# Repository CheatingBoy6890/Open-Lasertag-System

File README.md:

# Openlasertag-System
##This isn't maintained anymore and to be honest never really worked. Please have a look at Open-Lasertag-System-Tagger, we're continuing work there. 
--
Openlasertag-System is a project for the ESP32 and ESP8266 that aims
to make a Lasertag playebla for everyone without needing to setup a Wifi, servers etc.
---
The project is currently in Alpha state and not yet tested, but I'm trying my best to progress as fast as possible.

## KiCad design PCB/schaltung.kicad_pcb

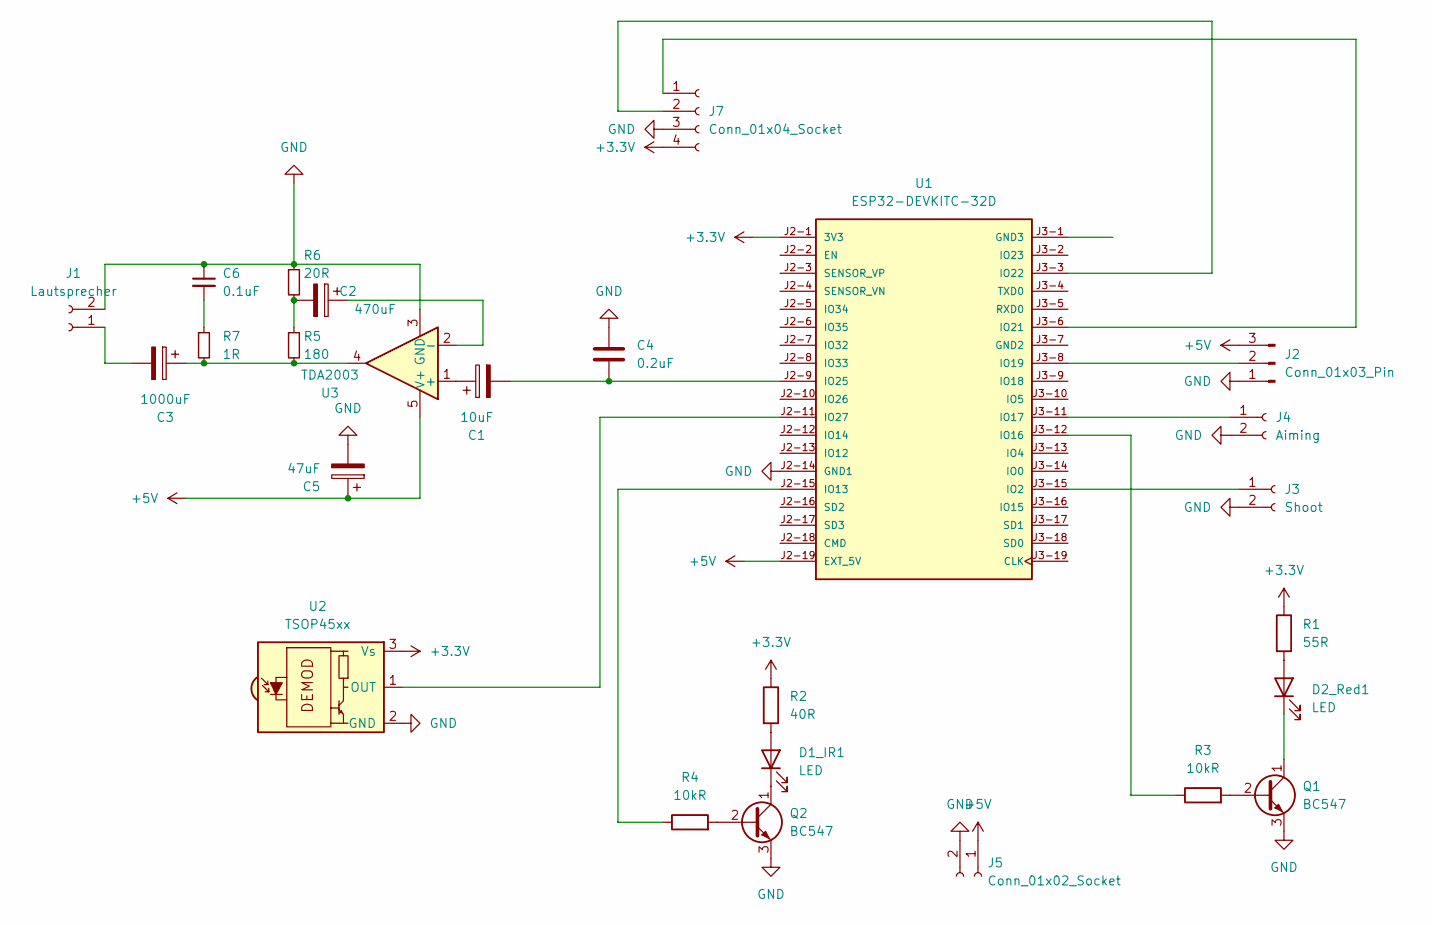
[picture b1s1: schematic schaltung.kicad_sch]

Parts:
C1: 10uF; CP_Radial_D4.0mm_P1.50mm
C2: 470uF; CP_Radial_D4.0mm_P1.50mm
C3: 1000uF; CP_Radial_D5.0mm_P2.50mm
C4: 0.2uF; C_Disc_D3.0mm_W1.6mm_P2.50mm
C5: 47uF; CP_Radial_D4.0mm_P1.50mm
C6: 0.1uF; C_Disc_D3.0mm_W1.6mm_P2.50mm
D1_IR1, D2_Red1: LED; LED_D1.8mm_W3.3mm_H2.4mm
J1: Lautsprecher; PinHeader_1x02_P1.00mm_Vertical
J2: Conn_01x03_Pin; PinHeader_1x03_P1.00mm_Vertical
J3: Shoot; PinHeader_1x02_P1.00mm_Vertical
J4: Aiming; PinHeader_1x02_P1.00mm_Vertical
J5: Conn_01x02_Socket; PinHeader_1x02_P1.00mm_Vertical
J7: Conn_01x04_Socket; PinHeader_1x04_P1.00mm_Vertical
Q1, Q2: BC547; TO-92_Inline
R1: 55R; R_Axial_DIN0204_L3.6mm_D1.6mm_P5.08mm_Horizontal
R2: 40R; R_Axial_DIN0204_L3.6mm_D1.6mm_P5.08mm_Horizontal
R3, R4: 10kR; R_Axial_DIN0204_L3.6mm_D1.6mm_P5.08mm_Horizontal
R5: 180; R_Axial_DIN0204_L3.6mm_D1.6mm_P5.08mm_Horizontal
R6: 20R; R_Axial_DIN0204_L3.6mm_D1.6mm_P5.08mm_Horizontal
R7: 1R; R_Axial_DIN0204_L3.6mm_D1.6mm_P5.08mm_Horizontal
U1: ESP32-DEVKITC-32D; MODULE_ESP32-DEVKITC-32D; PARTREV V4
U2: TSOP45xx; Vishay_MOLD-3Pin
U3: TDA2003; TO-220-5_P3.4x3.7mm_StaggerOdd_Lead3.8mm_Vertical

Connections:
+3.3V: J7.4, R1.1, R2.1, U1.J2-1 (3V3), U2.3 (Vs)
+5V: C5.1, J2.3, J5.1, U1.J2-19 (EXT_5V), U3.5 (V+)
GND: C4.1, C5.2, C6.1, J1.2, J2.1, J3.2, J4.2, J5.2, J7.3, Q1.3 (E), Q2.3 (E), R6.1, U1.J2-14 (GND1), U2.2 (GND), U3.3 (GND)
unnamed: C2.2, R5.1, R6.2
unnamed: C3.1, R5.2, R7.2, U3.4
unnamed: C6.2, R7.1
unnamed: D1_IR1.2 (A), R2.2
unnamed: D1_IR1.1 (K), Q2.1 (C)
unnamed: D2_Red1.2 (A), R1.2
unnamed: D2_Red1.1 (K), Q1.1 (C)
unnamed: C3.2, J1.1
unnamed: J2.2, U1.J3-8 (IO19)
unnamed: J3.1, U1.J3-15 (IO2)
unnamed: J4.1, U1.J3-11 (IO17)
unnamed: J7.1, U1.J3-6 (IO21)
unnamed: J7.2, U1.J3-3 (IO22)
unnamed: Q1.2 (B), R3.2
unnamed: Q2.2 (B), R4.2
unnamed: R4.1, U1.J2-15 (IO13)
unnamed: R3.1, U1.J3-12 (IO16)
unnamed: C1.2, C4.2, U1.J2-9 (IO25)
unnamed: U1.J2-11 (IO27), U2.1 (OUT)
unnamed: C1.1, U3.1 (+)
unnamed: C2.1, U3.2 (-)

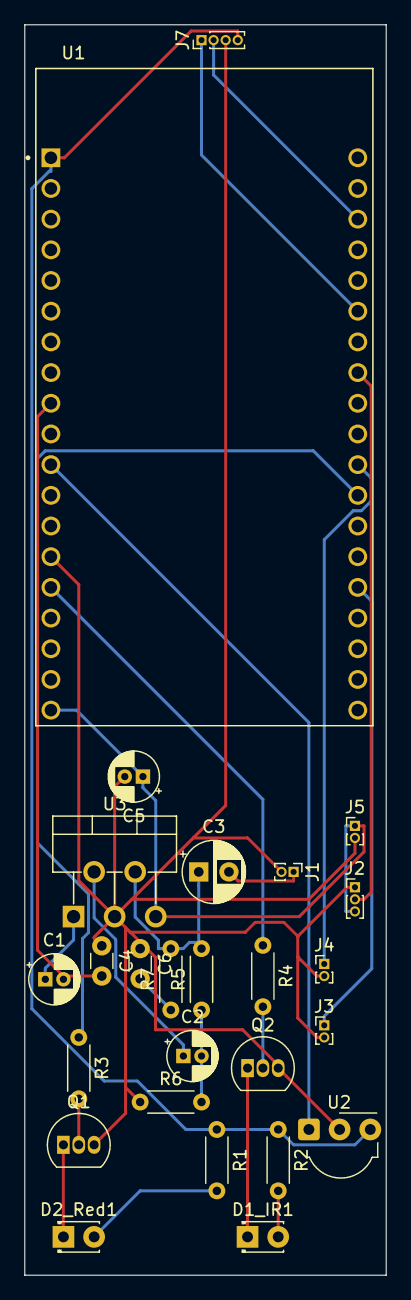
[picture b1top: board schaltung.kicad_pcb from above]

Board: 2 copper layers, 29.9 x 103.5 mm, 26 parts (0 on the bottom side), 24 nets.

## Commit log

2023-09-06 -Added KICad files for the PCB -Updated README
2023-09-06 modified: README.md
2023-09-09 PCB files moved to seperate repository.
